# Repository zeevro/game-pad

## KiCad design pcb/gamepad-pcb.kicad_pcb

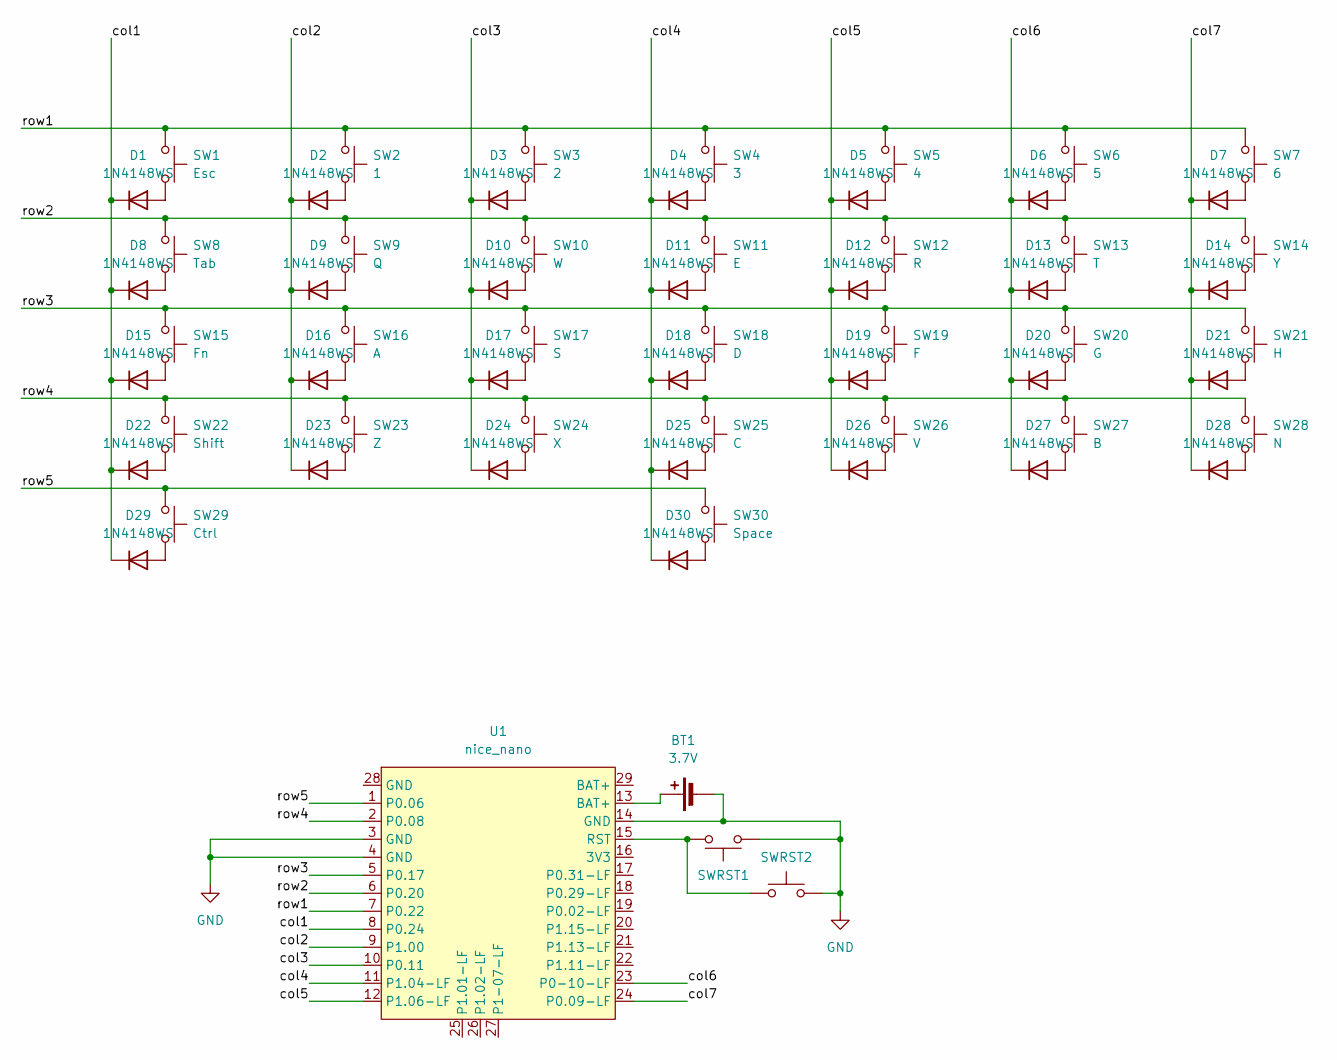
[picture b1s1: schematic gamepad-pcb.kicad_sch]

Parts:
BT1: 3.7V; PinHeader_1x02_P2.54mm_Vertical
D1, D2, D3, D4, D5, D6, D7, D8, D9, D10, D11, D12, D13, D14, D15, D16, D17, D18, D19, D20, D21, D22, D23, D24, D25, D26, D27, D28, D29, D30: 1N4148WS; D_SOD-323_HandSoldering
SW1: Esc; SW_Cherry_MX_PCB_1.00u
SW2: 1; SW_Cherry_MX_PCB_1.00u
SW3: 2; SW_Cherry_MX_PCB_1.00u
SW4: 3; SW_Cherry_MX_PCB_1.00u
SW5: 4; SW_Cherry_MX_PCB_1.00u
SW6: 5; SW_Cherry_MX_PCB_1.00u
SW7: 6; SW_Cherry_MX_PCB_1.00u
SW8: Tab; SW_Cherry_MX_PCB_1.50u
SW9: Q; SW_Cherry_MX_PCB_1.00u
SW10: W; SW_Cherry_MX_PCB_1.00u
SW11: E; SW_Cherry_MX_PCB_1.00u
SW12: R; SW_Cherry_MX_PCB_1.00u
SW13: T; SW_Cherry_MX_PCB_1.00u
SW14: Y; SW_Cherry_MX_PCB_1.00u
SW15: Fn; SW_Cherry_MX_PCB_1.25u
SW16: A; SW_Cherry_MX_PCB_1.00u
SW17: S; SW_Cherry_MX_PCB_1.00u
SW18: D; SW_Cherry_MX_PCB_1.00u
SW19: F; SW_Cherry_MX_PCB_1.00u
SW20: G; SW_Cherry_MX_PCB_1.00u
SW21: H; SW_Cherry_MX_PCB_1.00u
SW22: Shift; SW_Cherry_MX_PCB_1.75u
SW23: Z; SW_Cherry_MX_PCB_1.00u
SW24: X; SW_Cherry_MX_PCB_1.00u
SW25: C; SW_Cherry_MX_PCB_1.00u
SW26: V; SW_Cherry_MX_PCB_1.00u
SW27: B; SW_Cherry_MX_PCB_1.00u
SW28: N; SW_Cherry_MX_PCB_1.00u
SW29: Ctrl; SW_Cherry_MX_PCB_1.25u
SW30: Space; SW_Cherry_MX_PCB_6.25u
SWRST1, SWRST2: SW_SPST_B3U-1000P
U1: nice_nano; nice_nano_H_USBup

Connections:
/col1: D1.1 (K), D8.1 (K), D15.1 (K), D22.1 (K), D29.1 (K), U1.8 (P0.24)
/col2: D2.1 (K), D9.1 (K), D16.1 (K), D23.1 (K), U1.9 (P1.00)
/col3: D3.1 (K), D10.1 (K), D17.1 (K), D24.1 (K), U1.10 (P0.11)
/col4: D4.1 (K), D11.1 (K), D18.1 (K), D25.1 (K), D30.1 (K), U1.11 (P1.04-LF)
/col5: D5.1 (K), D12.1 (K), D19.1 (K), D26.1 (K), U1.12 (P1.06-LF)
/col6: D6.1 (K), D13.1 (K), D20.1 (K), D27.1 (K), U1.23 (P0-10-LF)
/col7: D7.1 (K), D14.1 (K), D21.1 (K), D28.1 (K), U1.24 (P0.09-LF)
/row1: SW1.1, SW2.1, SW3.1, SW4.1, SW5.1, SW6.1, SW7.1, U1.7 (P0.22)
/row2: SW8.1, SW9.1, SW10.1, SW11.1, SW12.1, SW13.1, SW14.1, U1.6 (P0.20)
/row3: SW15.1, SW16.1, SW17.1, SW18.1, SW19.1, SW20.1, SW21.1, U1.5 (P0.17)
/row4: SW22.1, SW23.1, SW24.1, SW25.1, SW26.1, SW27.1, SW28.1, U1.2 (P0.08)
/row5: SW29.1, SW30.1, U1.1 (P0.06)
GND: BT1.2 (-), SWRST1.2, SWRST2.2, U1.3 (GND), U1.4 (GND), U1.14 (GND)
unnamed: BT1.1 (+), U1.13 (BAT+)
unnamed: D1.2 (A), SW1.2
unnamed: D2.2 (A), SW2.2
unnamed: D3.2 (A), SW3.2
unnamed: D4.2 (A), SW4.2
unnamed: D5.2 (A), SW5.2
unnamed: D6.2 (A), SW6.2
unnamed: D7.2 (A), SW7.2
unnamed: D8.2 (A), SW8.2
unnamed: D9.2 (A), SW9.2
unnamed: D10.2 (A), SW10.2
unnamed: D11.2 (A), SW11.2
unnamed: D12.2 (A), SW12.2
unnamed: D13.2 (A), SW13.2
unnamed: D14.2 (A), SW14.2
unnamed: D15.2 (A), SW15.2
unnamed: D16.2 (A), SW16.2
unnamed: D17.2 (A), SW17.2
unnamed: D18.2 (A), SW18.2
unnamed: D19.2 (A), SW19.2
unnamed: D20.2 (A), SW20.2
unnamed: D21.2 (A), SW21.2
unnamed: D22.2 (A), SW22.2
unnamed: D23.2 (A), SW23.2
unnamed: D24.2 (A), SW24.2
unnamed: D25.2 (A), SW25.2
unnamed: D26.2 (A), SW26.2
unnamed: D27.2 (A), SW27.2
unnamed: D28.2 (A), SW28.2
unnamed: D29.2 (A), SW29.2
unnamed: D30.2 (A), SW30.2
unnamed: SWRST1.1, SWRST2.1, U1.15 (RST)

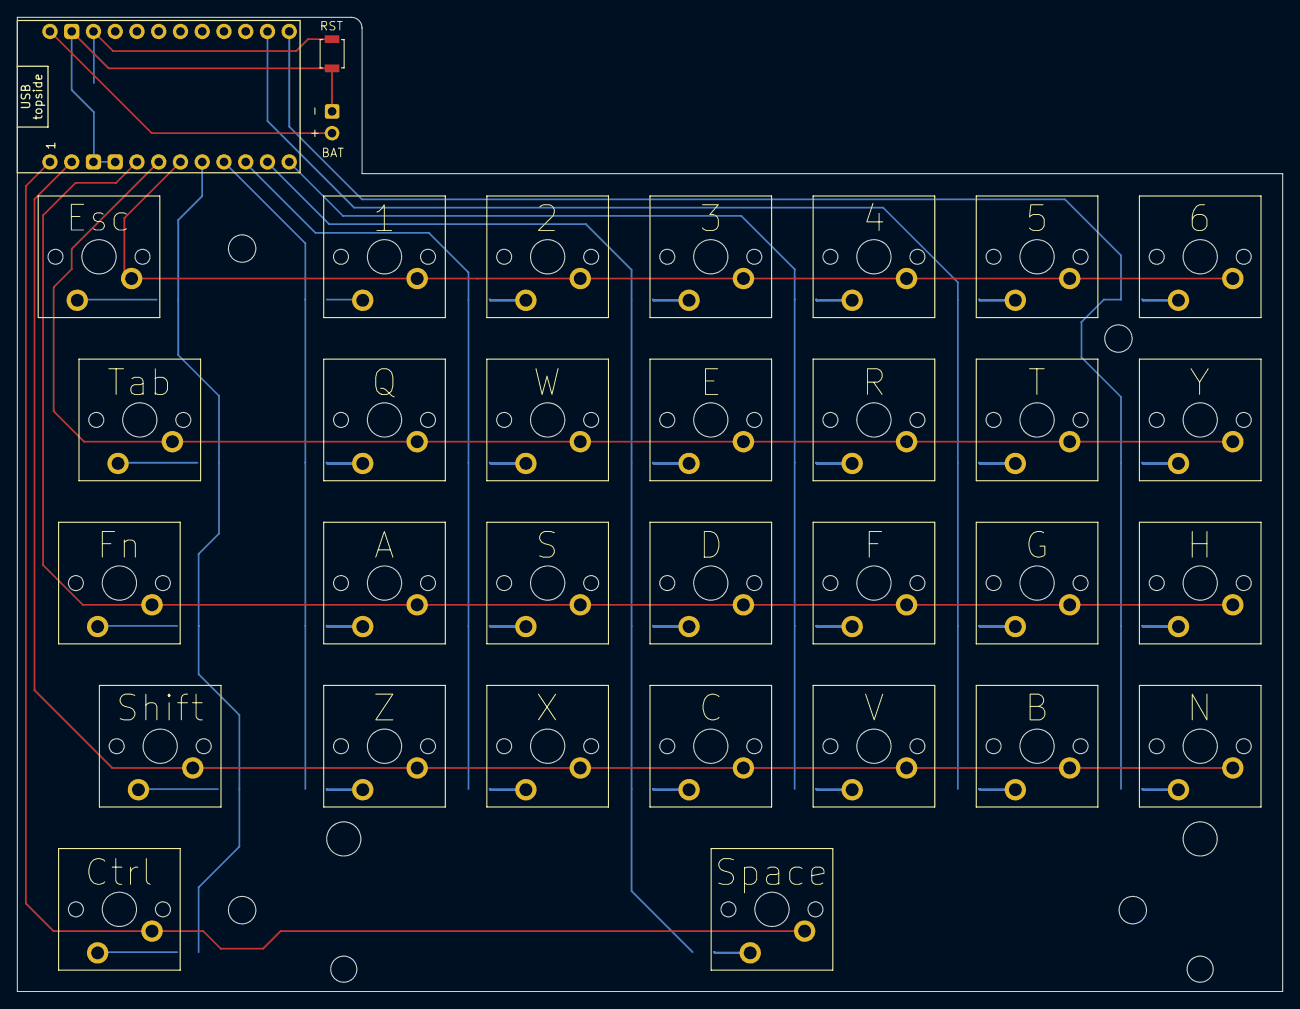
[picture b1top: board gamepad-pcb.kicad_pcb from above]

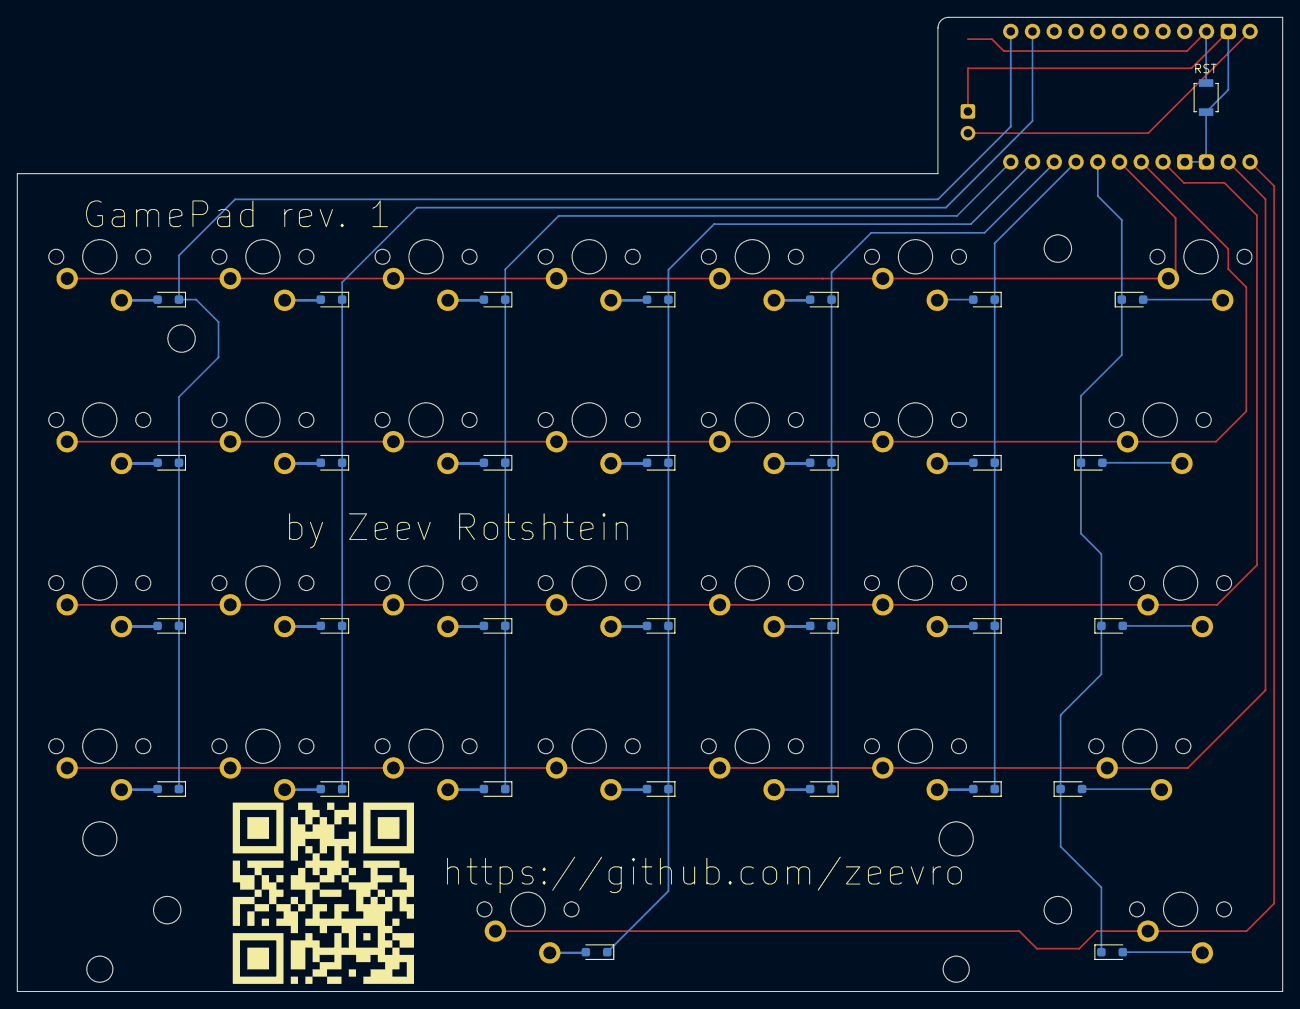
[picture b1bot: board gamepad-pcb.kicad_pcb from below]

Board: 2 copper layers, 147.8 x 113.8 mm, 70 parts (32 on the bottom side), 45 nets.

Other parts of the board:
MH1, MH2, MH3, MH3#2: MountingHole_3.2mm_M3
QR: LOGO
ST30: Stabilizer_Cherry_MX_6.25u

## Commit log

2024-05-12 wip 1
2024-05-16 wip 2
